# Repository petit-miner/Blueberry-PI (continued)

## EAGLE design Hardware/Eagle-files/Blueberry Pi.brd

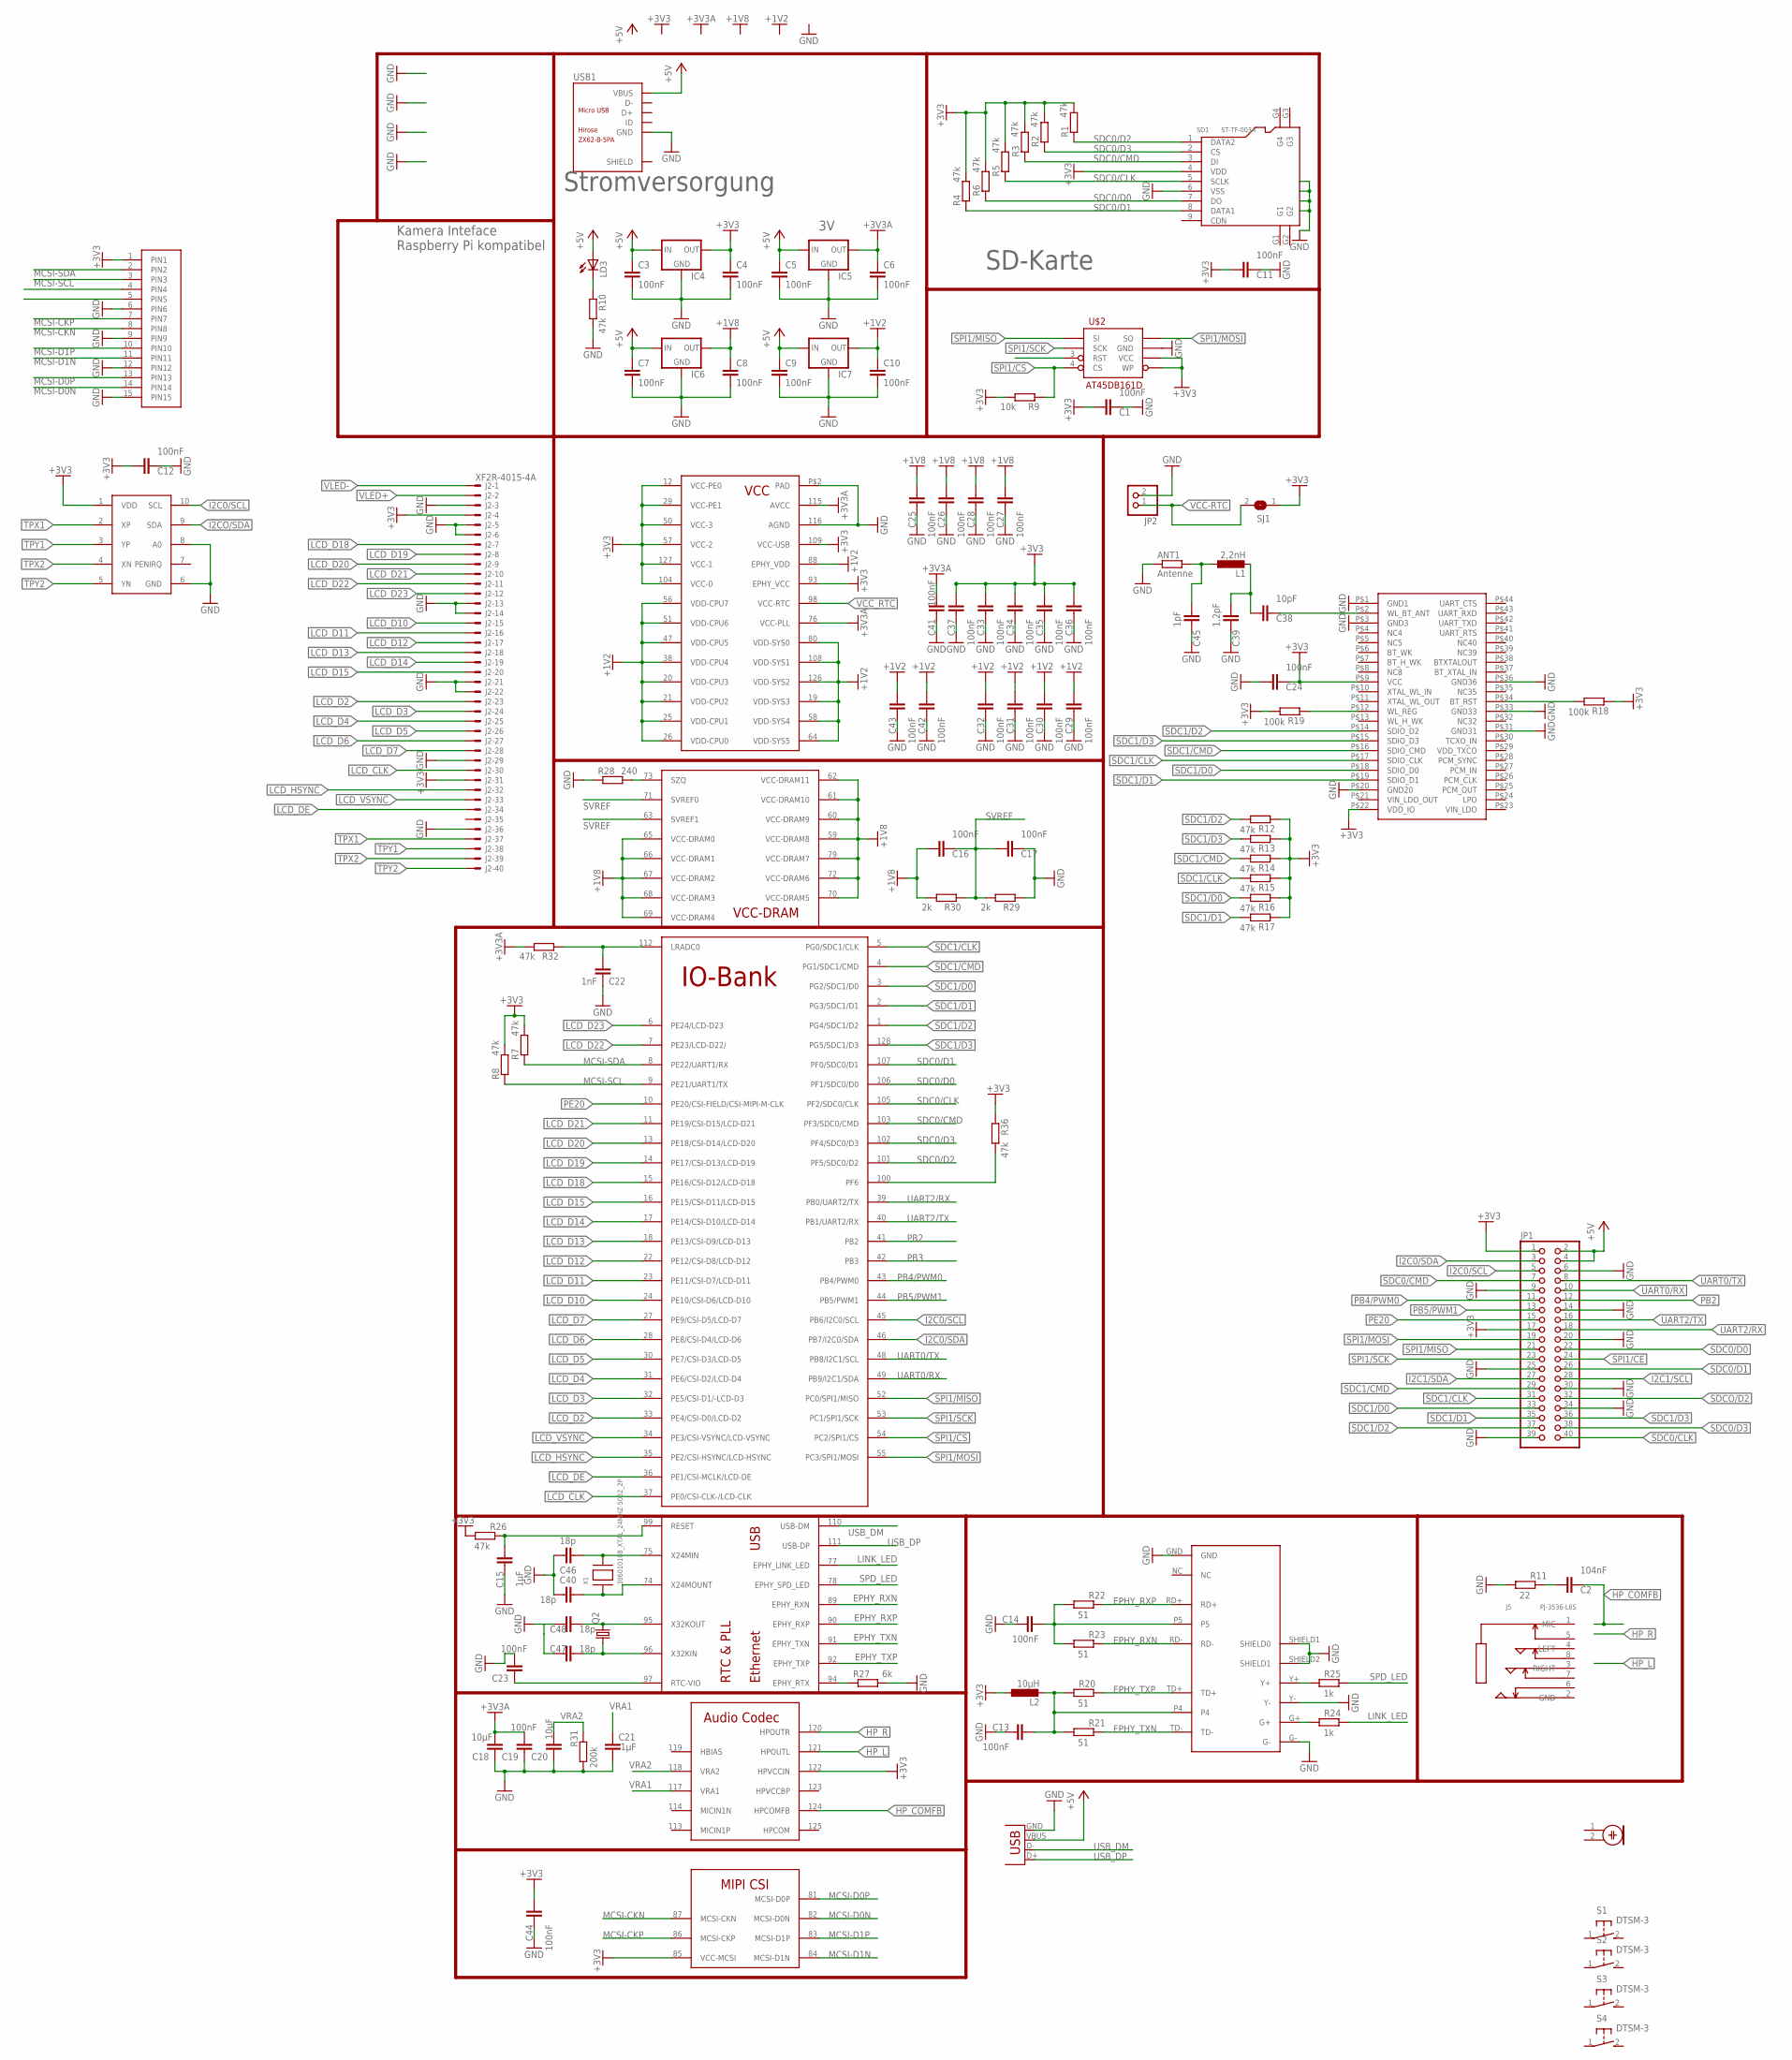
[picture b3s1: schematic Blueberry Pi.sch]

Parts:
ANT1: Antenne; R0603
C1, C3, C4, C5, C6, C7, C8, C9, C10, C11, C12, C13, C14, C16, C17, C19, C23, C24, C25, C26, C27, C28, C29, C30, C31, C32, C33, C34, C35, C36, C37, C41, C42, C43, C44: 100nF; C0603
C2: 104nF; C0603
C15, C21: 1µF; C0603
C18, C20: 10µF; C0603
C22: 1nF; C0603
C38: 10pF; C0603
C39: 1,2pF; C0603
C40, C46, C47, C48: 18p; C0603
C45: 1pF; C0603
IC1: V3S; QFP-128
IC4, IC5, IC6, IC7: LM1117; SOT223
J2: XF2R-4015-4A
J5: PJ-3536-L6S; AUDIO8P-SMD-3.5-14.5X6X5MM
JP1: PINHD-2X20; 2X20
JP2: PINHD-1X2; 1X02
L1: 2,2nH; L0805
L2: 10µH; L0805
LD3: LEDSMT1206; 1206
M1: ELECTRET_MICROPHON-F6035AP; F6035AP
Q2: CRYSTALTC26H; TC26H
R1, R2, R3, R4, R5, R6, R7, R8, R10, R12, R13, R14, R15, R16, R17, R26, R32, R36: 47k; R0603
R9: 10k; R0603
R11: 22; R0603
R18, R19: 100k; R0603
R20, R21, R22, R23: 51; R0603
R24, R25: 1k; R0603
R27: 6k; R0603
R28: 240; R0603
R29, R30: 2k; R0603
R31: 200k; R0603
S1, S2, S3, S4: DTSM-3
SD1: ST-TF-003A; MICRO-SD9+4P-SMD-16.1X14.5X1.85MM
SJ1: SJ
U$1: NS2009; MSOP10
U$2: AT45DB161D; SO08-EIAJ
U$3: HR911105A; RJ45
U$4: RTL8723BS; LGA
U$5: 52610-1533; MOLEX_52610-1533
USB1: ZX62-B-5PA; MICRO-USB5+6P-SMD-0.65-AB
X1: 306010108_XTAL_24MHZ-5032_2P; X5032_2P
X2: USB-A-H

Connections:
+1V2: C10.1, C29.1, C30.1, C31.1, C32.1, C42.1, C43.1, IC1.19 (VDD-SYS3), IC1.20 (VDD-CPU3), IC1.21 (VDD-CPU2), IC1.25 (VDD-CPU1), IC1.26 (VDD-CPU0), IC1.38 (VDD-CPU4), IC1.47 (VDD-CPU5), IC1.51 (VDD-CPU6), IC1.56 (VDD-CPU7), IC1.58 (VDD-SYS4), IC1.64 (VDD-SYS5), IC1.80 (VDD-SYS0), IC1.88 (EPHY_VDD), IC1.108 (VDD-SYS1), IC1.126 (VDD-SYS2), IC7.2 (OUT)
+1V8: C8.1, C16.1, C25.1, C26.1, C27.1, C28.1, IC1.59 (VCC-DRAM8), IC1.60 (VCC-DRAM9), IC1.61 (VCC-DRAM10), IC1.62 (VCC-DRAM11), IC1.65 (VCC-DRAM0), IC1.66 (VCC-DRAM1), IC1.67 (VCC-DRAM2), IC1.68 (VCC-DRAM3), IC1.69 (VCC-DRAM4), IC1.70 (VCC-DRAM5), IC1.72 (VCC-DRAM6), IC1.79 (VCC-DRAM7), IC6.2 (OUT), R30.2
+3V3: C1.1, C4.1, C11.1, C12.1, C24.2, C33.1, C34.1, C35.1, C36.1, C37.1, C44.1, IC1.12 (VCC-PE0), IC1.29 (VCC-PE1), IC1.50 (VCC-3), IC1.57 (VCC-2), IC1.85 (VCC-MCSI), IC1.93 (EPHY_VCC), IC1.104 (VCC-0), IC1.109 (VCC-USB), IC1.122 (HPVCCIN), IC1.127 (VCC-1), IC4.2 (OUT), J2.4 (MS), J2.31 (MS), JP1.1, JP1.17, L2.1, R1.2, R2.2, R3.2, R4.2, R5.2, R6.2, R7.2, R8.2, R9.2, R12.1, R13.1, R14.1, R15.1, R16.1, R17.1, R18.1, R19.2, R26.2, R36.1, SD1.4 (VDD), SJ1.1, U$1.1 (VDD), U$2.5 (WP), U$2.6 (VCC), U$4.P$9 (VCC), U$4.P$22 (VDD_IO), U$5.1 (PIN1)
+3V3A: C6.1, C18.1, C19.1, C41.1, IC1.76 (VCC-PLL), IC1.115 (AVCC), IC5.2 (OUT), R32.2
+5V: C3.1, C5.1, C7.1, C9.1, IC4.3 (IN), IC5.3 (IN), IC6.3 (IN), IC7.3 (IN), JP1.2, JP1.4, LD3.A, X2.VBUS
EPHY_RXN: IC1.89 (EPHY_RXN), R23.1, U$3.RD-
EPHY_RXP: IC1.90 (EPHY_RXP), R22.1, U$3.RD+
EPHY_TXN: IC1.91 (EPHY_TXN), R21.1, U$3.TD-
EPHY_TXP: IC1.92 (EPHY_TXP), R20.1, U$3.TD+
GND: ANT1.1, C1.2, C3.2, C4.2, C5.2, C6.2, C7.2, C8.2, C9.2, C10.2, C11.2, C12.2, C13.2, C14.2, C15.2, C17.2, C18.2, C19.2, C20.2, C21.2, C22.1, C23.1, C24.1, C25.2, C26.2, C27.2, C28.2, C29.2, C30.2, C31.2, C32.2, C33.2, C34.2, C35.2, C36.2, C37.2, C39.1, C40.1, C41.2, C42.2, C43.2, C44.2, C45.1, C46.1, C47.1, C48.1, IC1.116 (AGND), IC1.P$2 (PAD), IC4.1 (GND), IC5.1 (GND), IC6.1 (GND), IC7.1 (GND), J2.3 (MS), J2.5 (MS), J2.6 (MS), J2.13 (MS), J2.14 (MS), J2.21 (MS), J2.22 (MS), J2.29 (MS), J2.36 (MS), JP1.6, JP1.9, JP1.14, JP1.20, JP1.25, JP1.30, JP1.34, JP1.39, JP2.2, R10.2, R11.2, R27.2, R28.1, R29.1, R31.2, SD1.6 (VSS), U$1.6 (GND), U$1.8 (A0), U$2.7 (GND), U$3.G-, U$3.GND, U$3.SHIELD1 (SHIELD0), U$3.SHIELD2 (SHIELD1), U$3.Y-, U$4.P$1 (GND1), U$4.P$3 (GND3), U$4.P$20 (GND20), U$4.P$31 (GND31), U$4.P$33 (GND33), U$4.P$36 (GND36), U$5.6 (PIN6), U$5.9 (PIN9), U$5.12 (PIN12), U$5.15 (PIN15), USB1.5 (GND), X2.GND
HP_COMFB: C2.2, IC1.124 (HPCOMFB)
HP_L: IC1.121 (HPOUTL)
HP_R: IC1.120 (HPOUTR)
I2C0/SCL: IC1.45 (PB6/I2C0/SCL), JP1.5, U$1.10 (SCL)
I2C0/SDA: IC1.46 (PB7/I2C0/SDA), JP1.3
I2C1/SCL: JP1.28
I2C1/SDA: JP1.27
I2CO/SDA: U$1.9 (SDA)
LCD_CLK: IC1.37 (PE0/CSI-CLK-/LCD-CLK), J2.30 (MS)
LCD_D2: IC1.33 (PE4/CSI-D0/LCD-D2), J2.23 (MS)
LCD_D3: IC1.32 (PE5/CSI-D1/-LCD-D3), J2.24 (MS)
LCD_D4: IC1.31 (PE6/CSI-D2/LCD-D4), J2.25 (MS)
LCD_D5: IC1.30 (PE7/CSI-D3/LCD-D5), J2.26 (MS)
LCD_D6: IC1.28 (PE8/CSI-D4/LCD-D6), J2.27 (MS)
LCD_D7: IC1.27 (PE9/CSI-D5/LCD-D7), J2.28 (MS)
LCD_D10: IC1.24 (PE10/CSI-D6/LCD-D10), J2.15 (MS)
LCD_D11: IC1.23 (PE11/CSI-D7/LCD-D11), J2.16 (MS)
LCD_D12: IC1.22 (PE12/CSI-D8/LCD-D12), J2.17 (MS)
LCD_D13: IC1.18 (PE13/CSI-D9/LCD-D13), J2.18 (MS)
LCD_D14: IC1.17 (PE14/CSI-D10/LCD-D14), J2.19 (MS)
LCD_D15: IC1.16 (PE15/CSI-D11/LCD-D15), J2.20 (MS)
LCD_D18: IC1.15 (PE16/CSI-D12/LCD-D18), J2.7 (MS)
LCD_D19: IC1.14 (PE17/CSI-D13/LCD-D19), J2.8 (MS)
LCD_D20: IC1.13 (PE18/CSI-D14/LCD-D20), J2.9 (MS)
LCD_D21: IC1.11 (PE19/CSI-D15/LCD-D21), J2.10 (MS)
LCD_D22: IC1.7 (PE23/LCD-D22/), J2.11 (MS)
LCD_D23: IC1.6 (PE24/LCD-D23), J2.12 (MS)
LCD_DE: IC1.36 (PE1/CSI-MCLK/LCD-DE), J2.34 (MS)
LCD_HSYNC: IC1.35 (PE2/CSI-HSYNC/LCD-HSYNC), J2.32 (MS)
LCD_VSYNC: IC1.34 (PE3/CSI-VSYNC/LCD-VSYNC), J2.33 (MS)
LINK_LED: IC1.77 (EPHY_LINK_LED), R24.1
MCSI-CKN: IC1.87 (MCSI-CKN), U$5.8 (PIN8)
MCSI-CKP: IC1.86 (MCSI-CKP), U$5.7 (PIN7)
MCSI-D0N: IC1.82 (MCSI-D0N), U$5.14 (PIN14)
MCSI-D0P: IC1.81 (MCSI-D0P), U$5.13 (PIN13)
MCSI-D1N: IC1.84 (MCSI-D1N), U$5.11 (PIN11)
MCSI-D1P: IC1.83 (MCSI-D1P), U$5.10 (PIN10)
MCSI-SCL: IC1.9 (PE21/UART1/TX), R8.1, U$5.3 (PIN3)
MCSI-SDA: IC1.8 (PE22/UART1/RX), R7.1, U$5.2 (PIN2)
unnamed: R18.2, U$4.P$34 (BT_RST)
unnamed: C2.1, R11.1
unnamed: C15.1, IC1.99 (RESET), R26.1
unnamed: LD3.C, R10.1
unnamed: R19.1, U$4.P$12 (WL_REG)
unnamed: C38.2, U$4.P$2 (WL_BT_ANT)
unnamed: C38.1, C39.2, L1.2
unnamed: ANT1.2, C45.2, L1.1
unnamed: IC1.94 (EPHY_RTX), R27.1
unnamed: R24.2, U$3.G+
unnamed: IC1.73 (SZQ), R28.2
unnamed: R25.2, U$3.Y+
unnamed: C13.1, L2.2, R20.2, R21.2, U$3.P4
unnamed: C14.1, R22.2, R23.2, U$3.P5
unnamed: C22.2, IC1.112 (LRADC0), R32.1
unnamed: C23.2, IC1.97 (RTC-VIO)
unnamed: IC1.100 (PF6), R36.2
unnamed: C40.2, IC1.74 (X24MOUNT), X1.P$1
unnamed: C46.2, IC1.75 (X24MIN), X1.P$2
unnamed: C47.2, IC1.96 (X32KIN), Q2.1
unnamed: C48.2, IC1.95 (X32KOUT), Q2.2
PB2: IC1.41 (PB2), JP1.12
PB3: IC1.42 (PB3)
PB4/PWM0: IC1.43 (PB4/PWM0), JP1.11
PB5/PWM1: IC1.44 (PB5/PWM1), JP1.13
PE20: IC1.10 (PE20/CSI-FIELD/CSI-MIPI-M-CLK), JP1.15
SDC0/CLK: IC1.105 (PF2/SDC0/CLK), JP1.40, R5.1, SD1.5 (SCLK)
SDC0/CMD: IC1.103 (PF3/SDC0/CMD), JP1.7, R3.1, SD1.3 (DI)
SDC0/D0: IC1.106 (PF1/SDC0/D0), JP1.22, R6.1, SD1.7 (DO)
SDC0/D1: IC1.107 (PF0/SDC0/D1), JP1.26, R4.1, SD1.8 (DATA1)
SDC0/D2: IC1.101 (PF5/SDC0/D2), R1.1, SD1.1 (DATA2)
SDC0/D3: IC1.102 (PF4/SDC0/D3), JP1.38, R2.1, SD1.2 (CS)
SDC1/CLK: IC1.5 (PG0/SDC1/CLK), JP1.31, R15.2, U$4.P$17 (SDIO_CLK)
SDC1/CMD: IC1.4 (PG1/SDC1/CMD), JP1.29, R14.2, U$4.P$16 (SDIO_CMD)
SDC1/D0: IC1.3 (PG2/SDC1/D0), JP1.33, R16.2, U$4.P$18 (SDIO_D0)
SDC1/D1: IC1.2 (PG3/SDC1/D1), JP1.35, R17.2, U$4.P$19 (SDIO_D1)
SDC1/D2: IC1.1 (PG4/SDC1/D2), JP1.37, R12.2, U$4.P$14 (SDIO_D2)
SDC1/D3: IC1.128 (PG5/SDC1/D3), JP1.36, R13.2, U$4.P$15 (SDIO_D3)
SDCO/D2: JP1.32
SPD_LED: IC1.78 (EPHY_SPD_LED), R25.1
SPI1/CE: JP1.24
SPI1/CS: IC1.54 (PC2/SPI1/CS), R9.1, U$2.4 (CS)
SPI1/MISO: IC1.52 (PC0/SPI1/MISO), JP1.21, U$2.1 (SI)
SPI1/MOSI: IC1.55 (PC3/SPI1/MOSI), JP1.19, U$2.8 (SO)
SPI1/SCK: IC1.53 (PC1/SPI1/SCK), JP1.23, U$2.2 (SCK)
SVREF: C16.2, C17.1, IC1.63 (SVREF1), IC1.71 (SVREF0), R29.2, R30.1
TPX1: J2.37 (MS), U$1.2 (XP)
TPX2: J2.39 (MS), U$1.4 (XN)
TPY1: J2.38 (MS), U$1.3 (YP)
TPY2: J2.40 (MS), U$1.5 (YN)
UART0/RX: IC1.49 (PB9/I2C1/SDA), JP1.10
UART0/TX: IC1.48 (PB8/I2C1/SCL), JP1.8
UART2/RX: IC1.39 (PB0/UART2/TX), JP1.18
UART2/TX: IC1.40 (PB1/UART2/RX), JP1.16
USB_DM: IC1.110 (USB-DM), X2.D-
USB_DP: IC1.111 (USB-DP), X2.D+
VBUS: USB1.1 (VBUS)
VCC-RTC: JP2.1, SJ1.2
VCC_RTC: IC1.98 (VCC-RTC)
VLED+: J2.2 (MS)
VLED-: J2.1 (MSV)
VRA1: C21.1, IC1.117 (VRA1)
VRA2: C20.1, IC1.118 (VRA2), R31.1

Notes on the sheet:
Stromversorgung
Kamera Inteface Raspberry Pi kompatibel
SD-Karte

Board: 2 copper layers, 110 parts (2 on the bottom side), 100 nets, no tracks yet.

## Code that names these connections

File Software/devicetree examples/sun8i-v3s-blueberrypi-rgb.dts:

/dts-v1/;
#include "sun8i-v3s.dtsi"
#include "sunxi-common-regulators.dtsi"
#include <dt-bindings/input/input.h>
/ {

	model = "Blueberry Pi";
	compatible = "blueberrypi", "allwinner,sun8i-v3s";

	
	aliases {
		serial0 = &uart0;
		ethernet0 = &emac;
		
	};

	chosen {
		stdout-path = "serial0:115200n8";
		
		};

	leds {
	compatible = "gpio-leds";

	act_led {
		label = "act_led:green:usr";
		gpios = <&pio 1 2 GPIO_ACTIVE_HIGH>; /* PB2 */
		linux,default-trigger = "mmc0";
		default-state = "off";
	};
	};
	
	bridge {
		compatible = "dumb-vga-dac";
		#address-cells = <1>;
		#size-cells = <0>;
		status = "okay";
		ports {
			#address-cells = <1>;
			#size-cells = <0>;

			port@0 {
				reg = <0>;

				vga_bridge_in: endpoint {
					remote-endpoint = <&tcon0_out_vga>;
				};
			};

			port@1 {
				reg = <1>;

				vga_bridge_out: endpoint {
					remote-endpoint = <&vga_con_in>;
				};
			};
		};
	};

	vga {
		compatible = "vga-connector";

		port {
			vga_con_in: endpoint {
				remote-endpoint = <&vga_bridge_out>;
			};
		};
	};

};

&fb0 {
	status = "okay";
};


&de0 {
	status = "okay";
};

&display_clocks {
	status = "okay";
};

&mixer0 {
	status = "okay";
};


&tcon0 {
	pinctrl-names = "default";
	pinctrl-0 = <&rgb_pins>;
	status = "okay";
};

&tcon0_out {
	tcon0_out_vga: endpoint@0 {
		reg = <0>;
		remote-endpoint = <&vga_bridge_in>;
	};
};


&ehci0 {
        status = "okay";
}; 

&ohci0 {
        status = "okay";
}; 

&usb_otg {
	dr_mode = "otg";
	status = "okay";
};

&usbphy {
	usb0_id_det-gpio = <&pio 5 6 GPIO_ACTIVE_HIGH>;
	status = "okay";
};

&emac {
	allwinner,leds-active-high;
	status = "okay";
};

&mmc0 {
	pinctrl-0 = <&mmc0_pins>;
	pinctrl-names = "default";
	broken-cd;
	bus-width = <4>;
	vmmc-supply = <&reg_vcc3v3>;
	status = "okay";
};

&uart0 {
	pinctrl-0 = <&uart0_pins>;
	pinctrl-names = "default";
	status = "okay";
};

&spi0 {
	status = "okay";
};

&i2c0 {
	pinctrl-0 = <&i2c0_pins>;
	pinctrl-names = "default";
	status = "okay";
};

&lradc {
	vref-supply = <&reg_vcc3v0>;
	status = "okay";

	button@200 {
		label = "Volume Up";
		linux,code = <KEY_VOLUMEUP>;
		channel = <0>;
		voltage = <200000>;
	};

	button@400 {
		label = "Volume Down";
		linux,code = <KEY_VOLUMEDOWN>;
		channel = <0>;
		voltage = <400000>;
	};

	button@600 {
		label = "Select";
		linux,code = <KEY_SELECT>;
		channel = <0>;
		voltage = <600000>;
	};

	button@800 {
		label = "Start";
		linux,code = <KEY_OK>;
		channel = <0>;
		voltage = <800000>;
	};
};

&codec {
	allwinner,audio-routing = "Headphone", "HP", "Headphone", "HPCOM", "Mic", "MIC1";
	status = "okay";
};
		
&pio {

	rgb_pins: rgb_pins@0 {
	        pins = "PE0", "PE1", "PE2", "PE3", "PE4",
		       "PE5", "PE6", "PE7", "PE8", "PE9",
		       "PE10", "PE11", "PE12", "PE13", "PE14",
		       "PE15", "PE16", "PE17", "PE18", "PE19",
		       "PE23", "PE24";
	        function = "lcd";
    	};

	i2c0_pins: i2c0 {
		pins = "PB6", "PB7";
		function = "i2c0";
	};

	i2c1_pins: i2c1 {
		pins = "PE21", "PE22";
		function = "i2c1";
	};
	

	uart0_pins: uart0@0 {
	 	pins = "PB8", "PB9";
		function = "uart0";
	};

};

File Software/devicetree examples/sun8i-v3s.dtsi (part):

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		
		
		mmc0_pins: mmc0@0 {
			pins = "PF0", "PF1", "PF2", "PF3", "PF4", "PF5";
			function = "mmc0";
			drive-strength = <30>;
			bias-pull-up;
		};

		mmc1_pins: mmc1 {
			pins = "PG0", "PG1", "PG2", "PG3", "PG4", "PG5";
			function = "mmc1";
			drive-strength = <30>;
			bias-pull-up;
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		};

		spi0_pins: spi0@0 {
			pins = "PC0", "PC1", "PC2", "PC3";
			function = "spi0";
			drive-strength = <30>;
			bias-pull-up;
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
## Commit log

2017-07-21 Added Hardware folder
2018-02-25 upload new design
2018-04-01 Create LICENSE
2018-06-14 New designstage
2018-06-21 first-prototype
2018-07-23 new devicetree files
2018-08-14 updated schematics
2018-08-31 uploaded new defconfig for Buildroot
2018-12-20 new version
2018-12-26 added German documentation
